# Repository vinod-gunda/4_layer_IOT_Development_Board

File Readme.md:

# 4-Layer ESP32-C3 Development Board

A custom **4-layer ESP32-C3 development board** designed from scratch using **KiCad 10** as part of my embedded systems and PCB design learning.

## Key Features

- ESP32-C3 based controller
- USB-C, USB-UART, Li-Po charging and power management
- SD Card, Flash Memory and sensor interfaces
- 4-layer PCB with power and GND distribution

## PCB Design Skills

- Custom schematic symbol design
- Custom footprint design
- Custom logo-to-footprint conversion
- Hierarchical schematic design
- PCB layout, routing and DRC verification

## Tools & Technology

- **KiCad 10**
- **ESP32-C3**
- **4-Layer PCB**

## Repository Contents

- KiCad schematic files
- PCB layout files
- Custom symbols and footprints
- Project images

## Purpose

This project was developed for **learning, prototyping, and improving practical PCB design skills**.

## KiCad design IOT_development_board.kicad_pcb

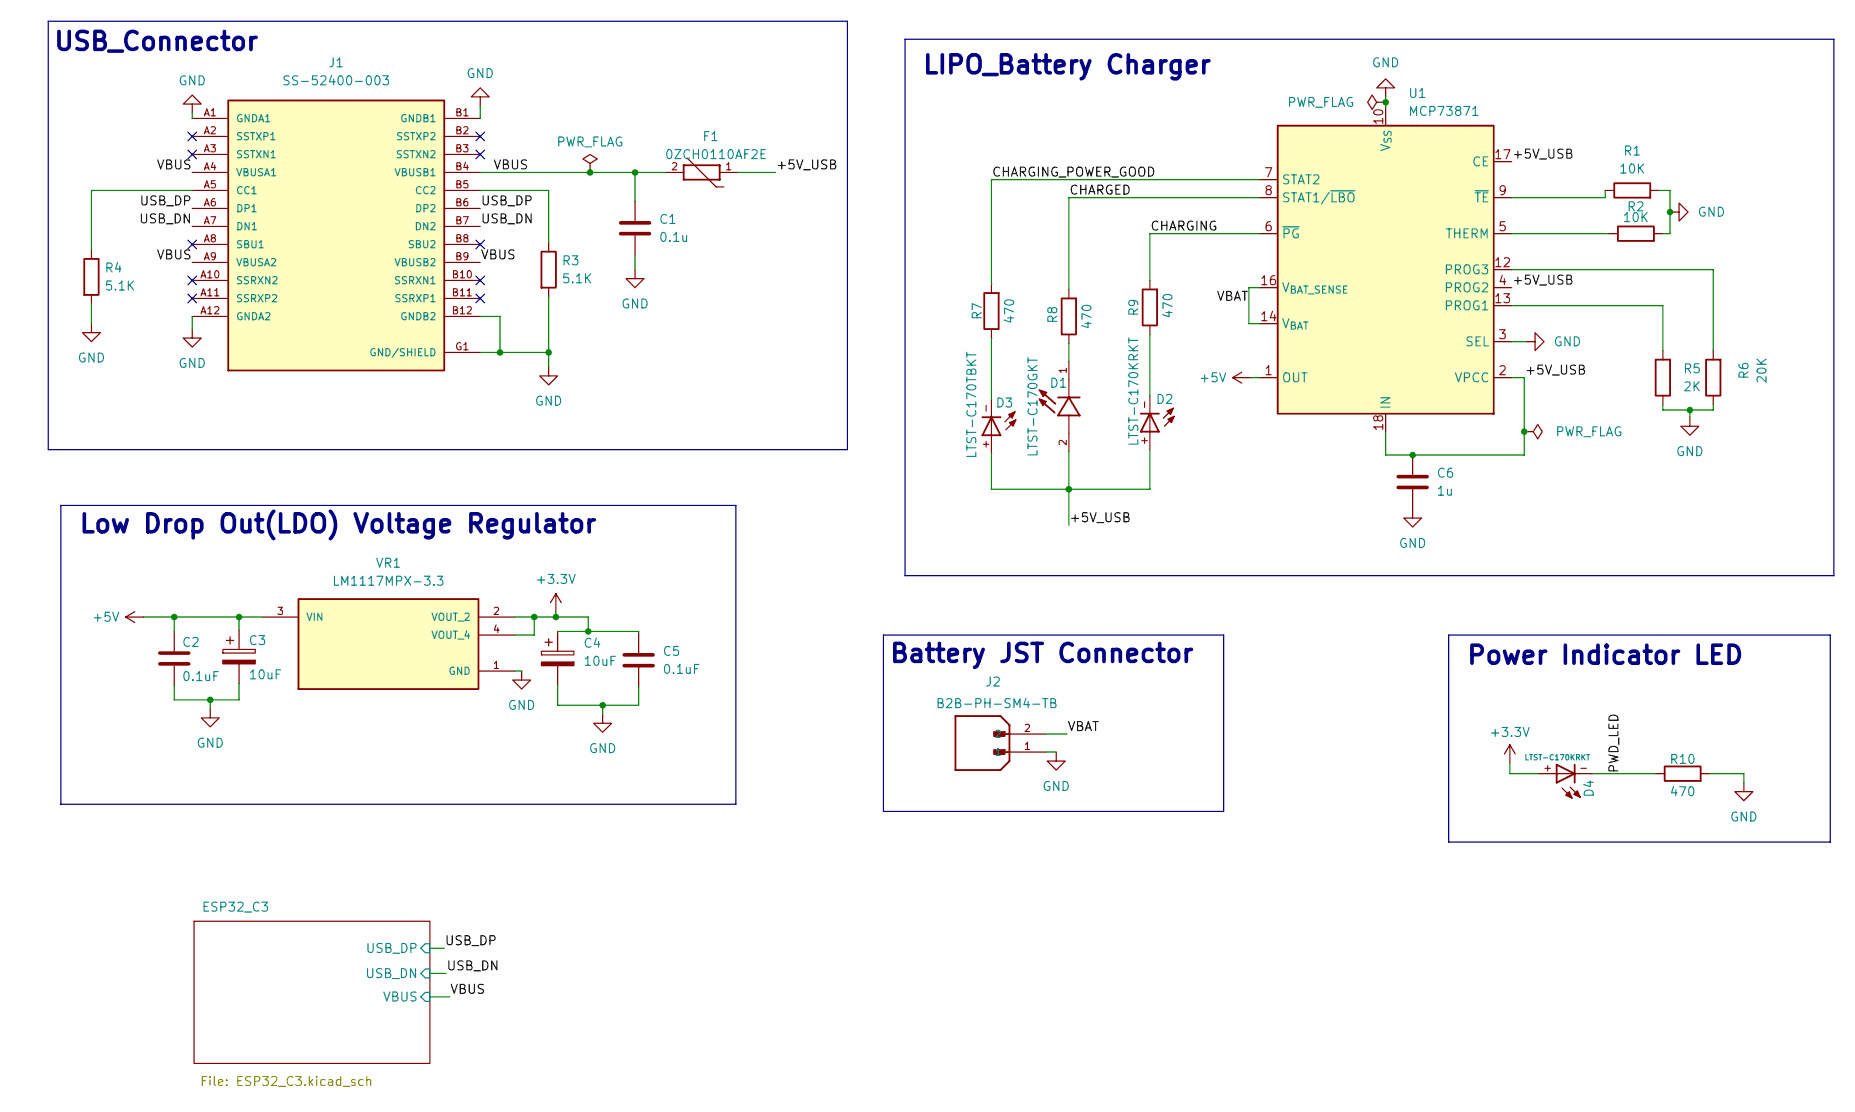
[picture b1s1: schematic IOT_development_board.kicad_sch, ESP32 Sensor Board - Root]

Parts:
C1: 0.1u; C_0805_2012Metric
C2, C5: 0.1uF; C_0805_2012Metric
C3, C4: 10uF; CT1206
C6: 1u; C_0805_2012Metric
D1: LTST-C170GKT; LED_LTST-C170GKT; PARTREV I
D2, D4: LTST-C170KRKT; DIOC200X125X110
D3: LTST-C170TBKT; DIOC200X125X110
F1: 0ZCH0110AF2E; FUSC3225X100N; PARTREV Apr2023
J1: SS-52400-003; BELFUSE_SS-52400-003; PARTREV A0
J2: B2B-PH-SM4-TB; JST_B2B-PH-SM4-TB; PARTREV N/A
R1, R2: 10K; R_0805_2012Metric
R3, R4: 5.1K; R_0805_2012Metric
R5: 2K; R_0805_2012Metric
R6: 20K; R_0805_2012Metric
R7, R8, R9, R10: 470; R_0805_2012Metric
U1: MCP73871; QFN-20-1EP_4x4mm_P0.5mm_EP2.5x2.5mm
VR1: LM1117MPX-3.3; VREG_LM1117MPX-3.3; PARTREV O

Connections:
+3.3V: C4.1, C5.1, D4.+, VR1.2 (VOUT_2), VR1.4 (VOUT_4); also elsewhere on the board
+5V: C2.1, C3.1, U1.1 (OUT), U1.20 (OUT), VR1.3 (VIN)
/+5V_USB: C6.1, D1.2, D2.+, D3.+, F1.1, U1.2 (VPCC), U1.4 (PROG2), U1.17 (CE), U1.18 (IN), U1.19 (IN)
/CHARGED: R8.2, U1.8 (STAT1/~LBO)
/CHARGING: R9.2, U1.6 (~PG)
/CHARGING_POWER_GOOD: R7.2, U1.7 (STAT2)
/PWD_LED: D4.-, R10.1
/USB_DN: J1.A7 (DN1), J1.B7 (DN2); also elsewhere on the board
/USB_DP: J1.A6 (DP1), J1.B6 (DP2); also elsewhere on the board
/VBAT: J2.2, U1.14 (V_{BAT}), U1.15 (V_{BAT}), U1.16 (V_{BAT_SENSE})
/VBUS: C1.1, F1.2, J1.A4 (VBUSA1), J1.A9 (VBUSA2), J1.B4 (VBUSB1), J1.B9 (VBUSB2); also elsewhere on the board
GND: C1.2, C2.2, C3.2, C4.2, C5.2, C6.2, J1.A1 (GNDA1), J1.A12 (GNDA2), J1.B1 (GNDB1), J1.B12 (GNDB2), J1.G1 (GND/SHIELD), J1.G2 (GND/SHIELD), J1.G3 (GND/SHIELD), J1.G4 (GND/SHIELD), J1.S1 (GND/SHIELD), J1.S2 (GND/SHIELD), J1.S3 (GND/SHIELD), J1.S4 (GND/SHIELD), J2.1, R1.2, R2.2, R3.2, R4.2, R5.1, R6.1, R10.2, U1.3 (SEL), U1.10 (V_{SS}), U1.11 (V_{SS}), U1.21 (V_{SS}), VR1.1 (GND); also elsewhere on the board
unnamed: D1.1, R8.1
unnamed: D2.-, R9.1
unnamed: D3.-, R7.1
unnamed: J1.A5 (CC1), R4.1
unnamed: J1.B5 (CC2), R3.1
unnamed: R5.2, U1.13 (PROG1)
unnamed: R6.2, U1.12 (PROG3)
unnamed: R2.1, U1.5 (THERM)
unnamed: R1.1, U1.9 (~TE)

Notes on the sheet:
LIPO_Battery Charger
Battery JST Connector
Power Indicator LED
Low Drop Out(LDO) Voltage Regulator
USB_Connector

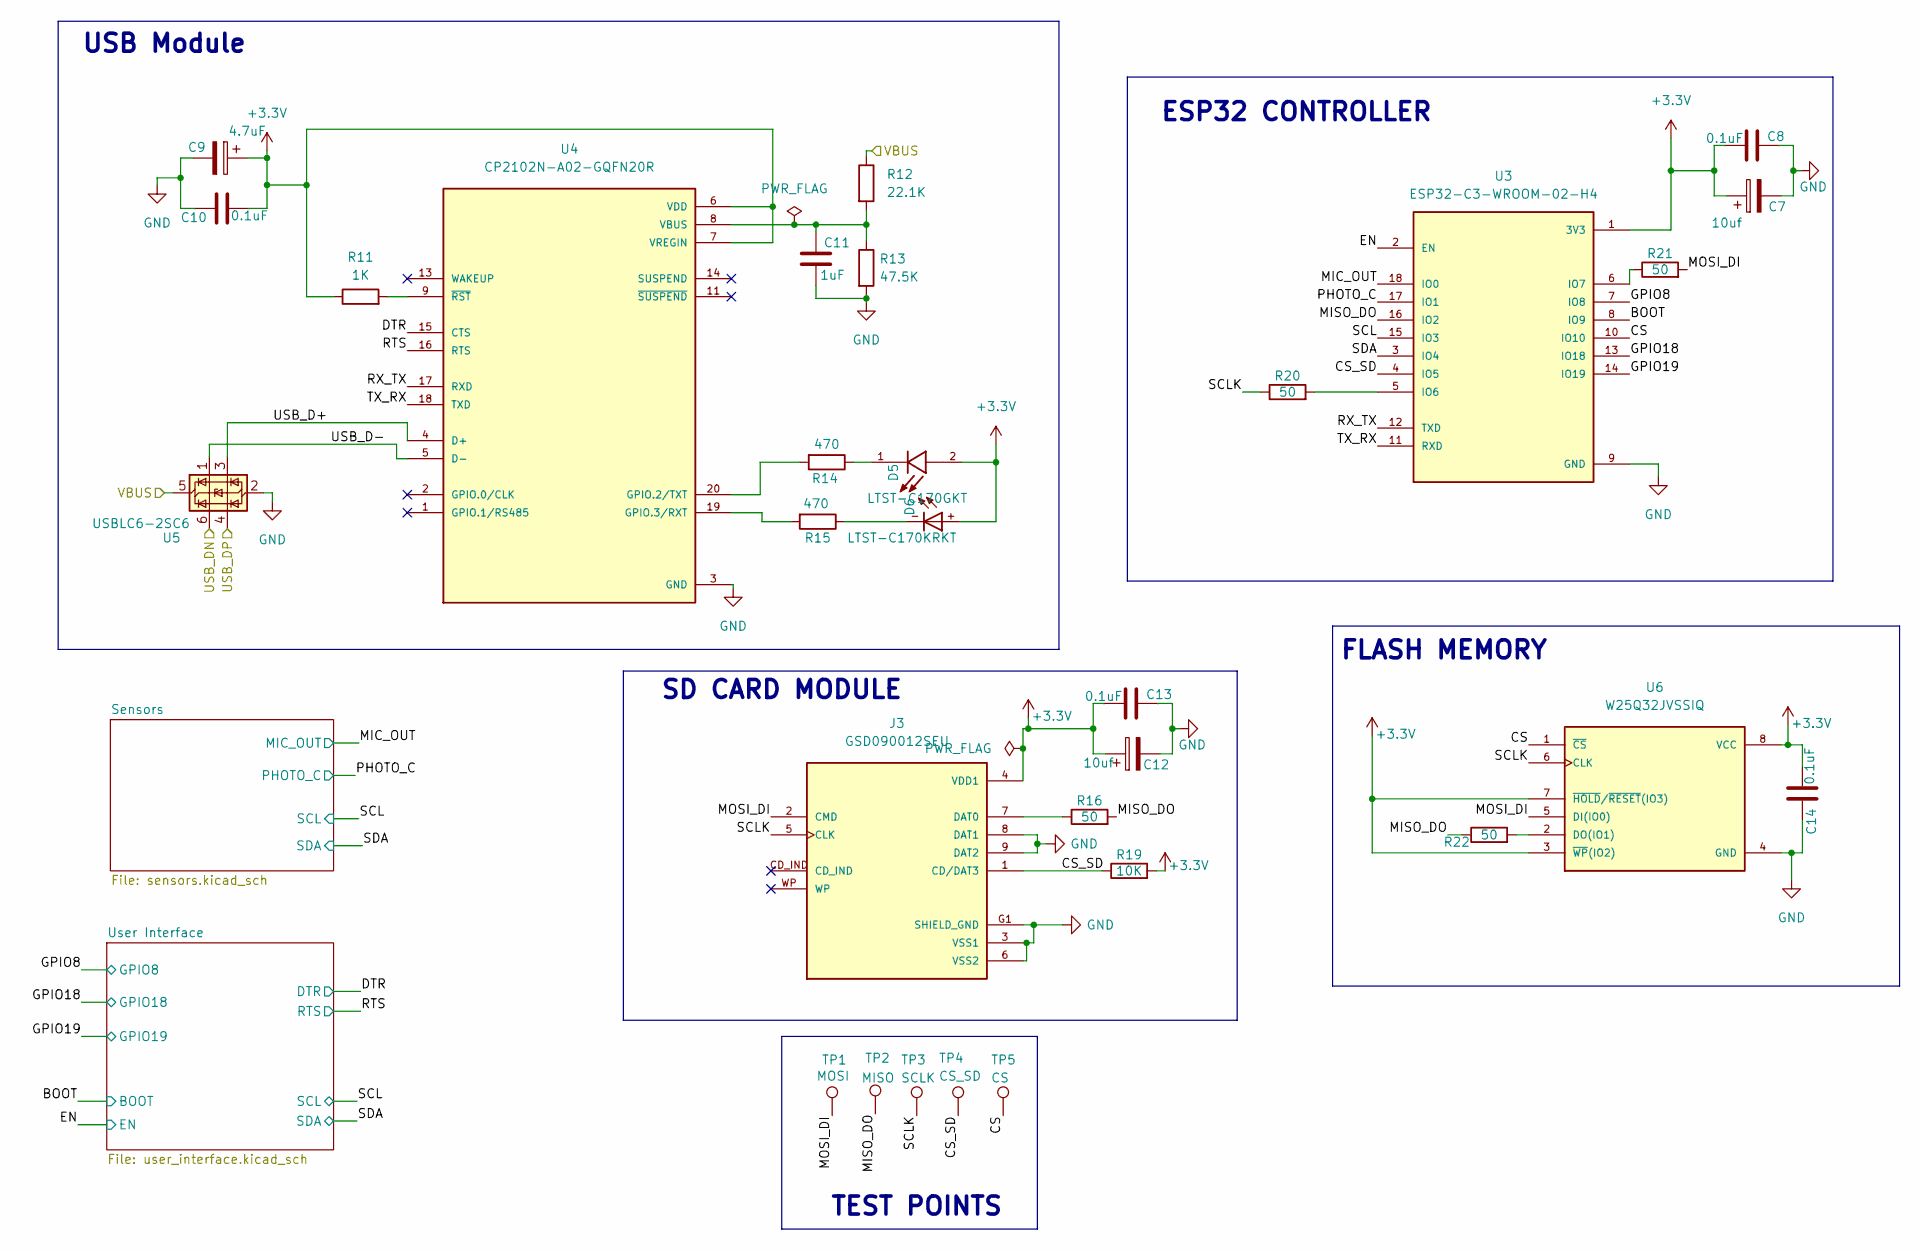
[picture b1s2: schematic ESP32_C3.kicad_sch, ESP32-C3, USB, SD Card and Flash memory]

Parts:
C7, C12: 10uf; CT1206
C8, C10, C13, C14: 0.1uF; C_0805_2012Metric
C9: 4.7uF; CT1206
C11: 1uF; C_0805_2012Metric
D5: LTST-C170GKT; LED_LTST-C170GKT; PARTREV I
D6: LTST-C170KRKT; DIOC200X125X110
J3: GSD090012SEU; AMPHENOL_GSD090012SEU; PARTREV E
R11: 1K; R_0805_2012Metric
R12: 22.1K; R_0805_2012Metric
R13: 47.5K; R_0805_2012Metric
R14, R15: 470; R_0805_2012Metric
R16, R20, R21, R22: 50; R_0805_2012Metric
R19: 10K; R_0805_2012Metric
TP1: MOSI; TestPoint_Pad_D1.0mm
TP2: MISO; TestPoint_Pad_D1.0mm
TP3: SCLK; TestPoint_Pad_D1.0mm
TP4: CS_SD; TestPoint_Pad_D1.0mm
TP5: CS; TestPoint_Pad_D1.0mm
U3: ESP32-C3-WROOM-02-H4; MODULE_ESP32-C3-WROOM-02-H4
U4: CP2102N-A02-GQFN20R; SILABS_CP2102N-A02-GQFN20R; PARTREV 1.3
U5: USBLC6-2SC6; SOT-23-6
U6: W25Q32JVSSIQ; SOIC127P790X216-8N; M_PART_NUMBER W25QXX

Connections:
+3.3V: C7.1, C8.2, C9.1, C10.2, C12.1, C13.2, C14.2, D5.2, D6.+, J3.4 (VDD1), R11.1, R19.2, U3.1 (3V3), U4.6 (VDD), U4.7 (VREGIN), U6.3 (~WP(IO2)), U6.7 (~HOLD/~RESET(IO3)), U6.8 (VCC); also elsewhere on the board
/ESP32_C3/CS: TP5.1 (1_1), U3.10 (IO10), U6.1 (~CS)
/ESP32_C3/EN: U3.2 (EN); also elsewhere on the board
/ESP32_C3/GPIO8: U3.7 (IO8); also elsewhere on the board
/ESP32_C3/GPIO18: U3.13 (IO18); also elsewhere on the board
/ESP32_C3/GPIO19: U3.14 (IO19); also elsewhere on the board
/ESP32_C3/MISO_DO: R16.2, R22.1, TP2.1 (1_1), U3.16 (IO2)
/ESP32_C3/MOSI_DI: J3.2 (CMD), R21.2, TP1.1 (1_1), U6.5 (DI(IO0))
/ESP32_C3/PHOTO_C: U3.17 (IO1); also elsewhere on the board
/ESP32_C3/RTS: U4.16 (RTS); also elsewhere on the board
/ESP32_C3/RX_TX: U3.12 (TXD), U4.17 (RXD)
/ESP32_C3/SCL: U3.15 (IO3); also elsewhere on the board
/ESP32_C3/SCLK: J3.5 (CLK), R20.1, TP3.1 (1_1), U6.6 (CLK)
/ESP32_C3/SDA: U3.3 (IO4); also elsewhere on the board
/ESP32_C3/TX_RX: U3.11 (RXD), U4.18 (TXD)
/ESP32_C3/USB_D+: U4.4 (D+), U5.3 (I/O2)
/ESP32_C3/USB_D-: U4.5 (D-), U5.1 (I/O1)
/USB_DN: U5.6 (I/O1); also elsewhere on the board
/USB_DP: U5.4 (I/O2); also elsewhere on the board
/VBUS: R12.1, U5.5 (VBUS); also elsewhere on the board
GND: C7.2, C8.1, C9.2, C10.1, C11.2, C12.2, C13.1, C14.1, J3.3 (VSS1), J3.6 (VSS2), J3.8 (DAT1), J3.9 (DAT2), J3.G1 (SHIELD_GND), J3.G2 (SHIELD_GND), J3.G3 (SHIELD_GND), J3.G4 (SHIELD_GND), R13.2, U3.9 (GND), U3.19 (GND), U3.20 (GND), U3.21 (GND), U3.22 (GND), U3.23 (GND), U3.24 (GND), U3.25 (GND), U3.26 (GND), U3.27 (GND), U3.28 (GND), U3.29 (GND), U3.30 (GND), U3.31 (GND), U3.32 (GND), U3.33 (GND), U3.34 (GND), U3.35 (GND), U3.36 (GND), U3.37 (GND), U3.38 (GND), U3.39 (GND), U4.3 (GND), U4.12 (GND), U4.21 (GND), U5.2 (GND), U6.4 (GND); also elsewhere on the board
unnamed: D5.1, R14.1
unnamed: D6.-, R15.1
unnamed: J3.7 (DAT0), R16.1
unnamed: R20.2, U3.5 (IO6)
unnamed: R21.1, U3.6 (IO7)
unnamed: R14.2, U4.20 (GPIO.2/TXT)
unnamed: R15.2, U4.19 (GPIO.3/RXT)
unnamed: C11.1, R12.2, R13.1, U4.8 (VBUS)
unnamed: R11.2, U4.9 (~RST)
unnamed: R22.2, U6.2 (DO(IO1))

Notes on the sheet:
TEST POINTS
FLASH MEMORY
ESP32 CONTROLLER
SD CARD MODULE
USB Module

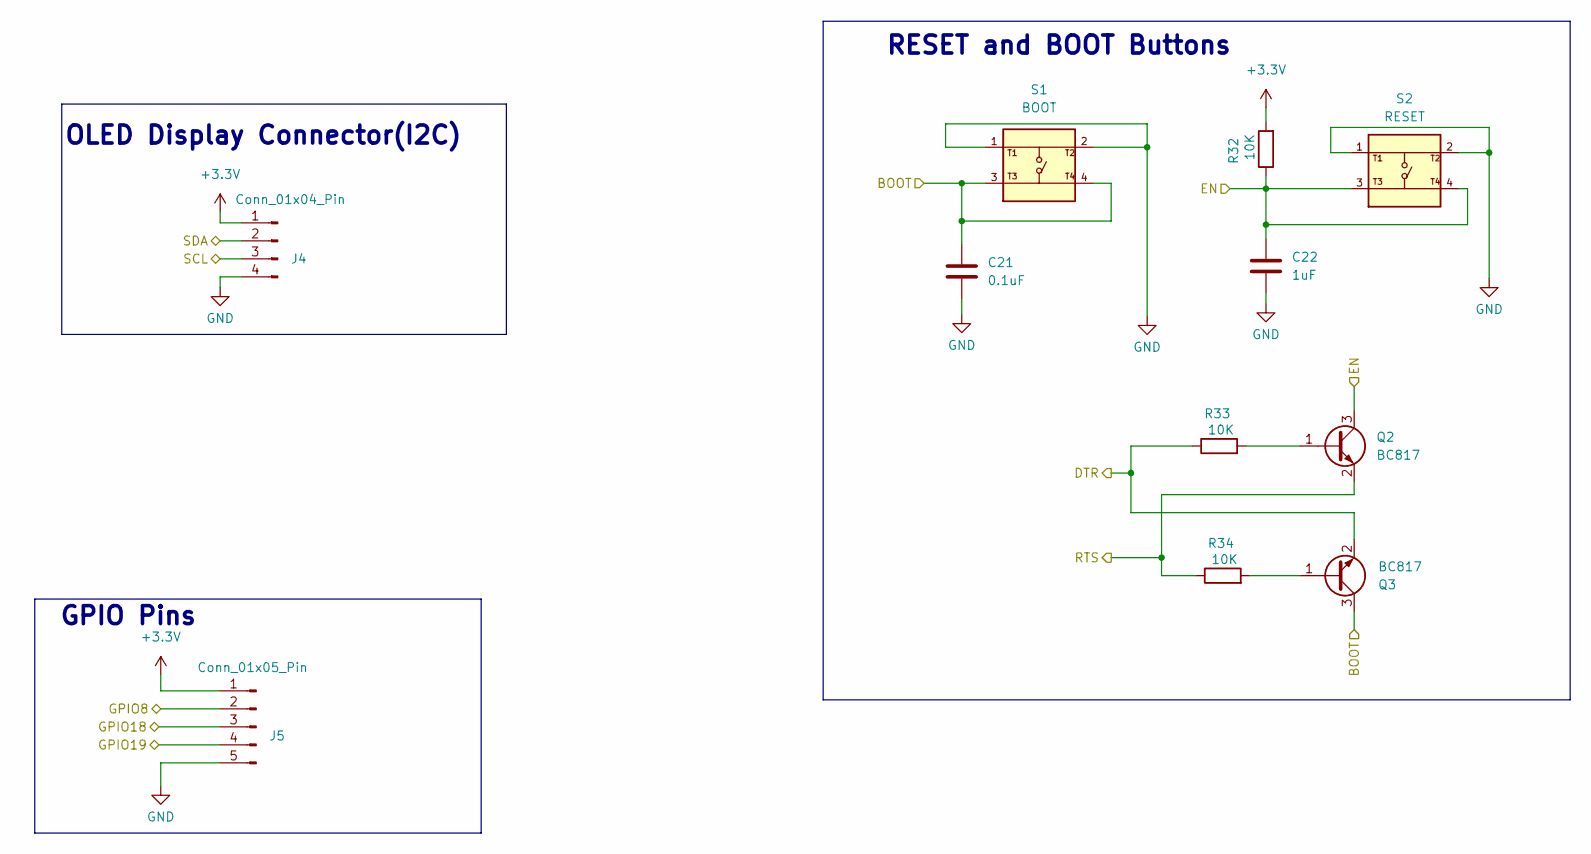
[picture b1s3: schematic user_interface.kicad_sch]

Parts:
C21: 0.1uF; C_0805_2012Metric
C22: 1uF; C_0805_2012Metric
J4: Conn_01x04_Pin; PinHeader_1x04_P2.54mm_Vertical
J5: Conn_01x05_Pin; PinHeader_1x05_P2.54mm_Vertical
Q2, Q3: BC817; SOT-23
R32, R33, R34: 10K; R_0805_2012Metric
S1: BOOT; SW_USLPT2819DT2TR; PARTREV P
S2: RESET; SW_USLPT2819DT2TR; PARTREV P

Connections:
+3.3V: J4.1, J5.1, R32.2; also elsewhere on the board
/ESP32_C3/EN: C22.1, Q2.3 (C), R32.1, S2.3, S2.4; also elsewhere on the board
/ESP32_C3/GPIO8: J5.2; also elsewhere on the board
/ESP32_C3/GPIO18: J5.3; also elsewhere on the board
/ESP32_C3/GPIO19: J5.4; also elsewhere on the board
/ESP32_C3/RTS: Q2.2 (E), R34.1; also elsewhere on the board
/ESP32_C3/SCL: J4.3; also elsewhere on the board
/ESP32_C3/SDA: J4.2; also elsewhere on the board
GND: C21.2, C22.2, J4.4, J5.5, S1.1, S1.2, S2.1, S2.2; also elsewhere on the board
unnamed: Q2.1 (B), R33.2
unnamed: Q3.1 (B), R34.2

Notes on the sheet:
OLED Display Connector(I2C)
RESET and BOOT Buttons
GPIO Pins

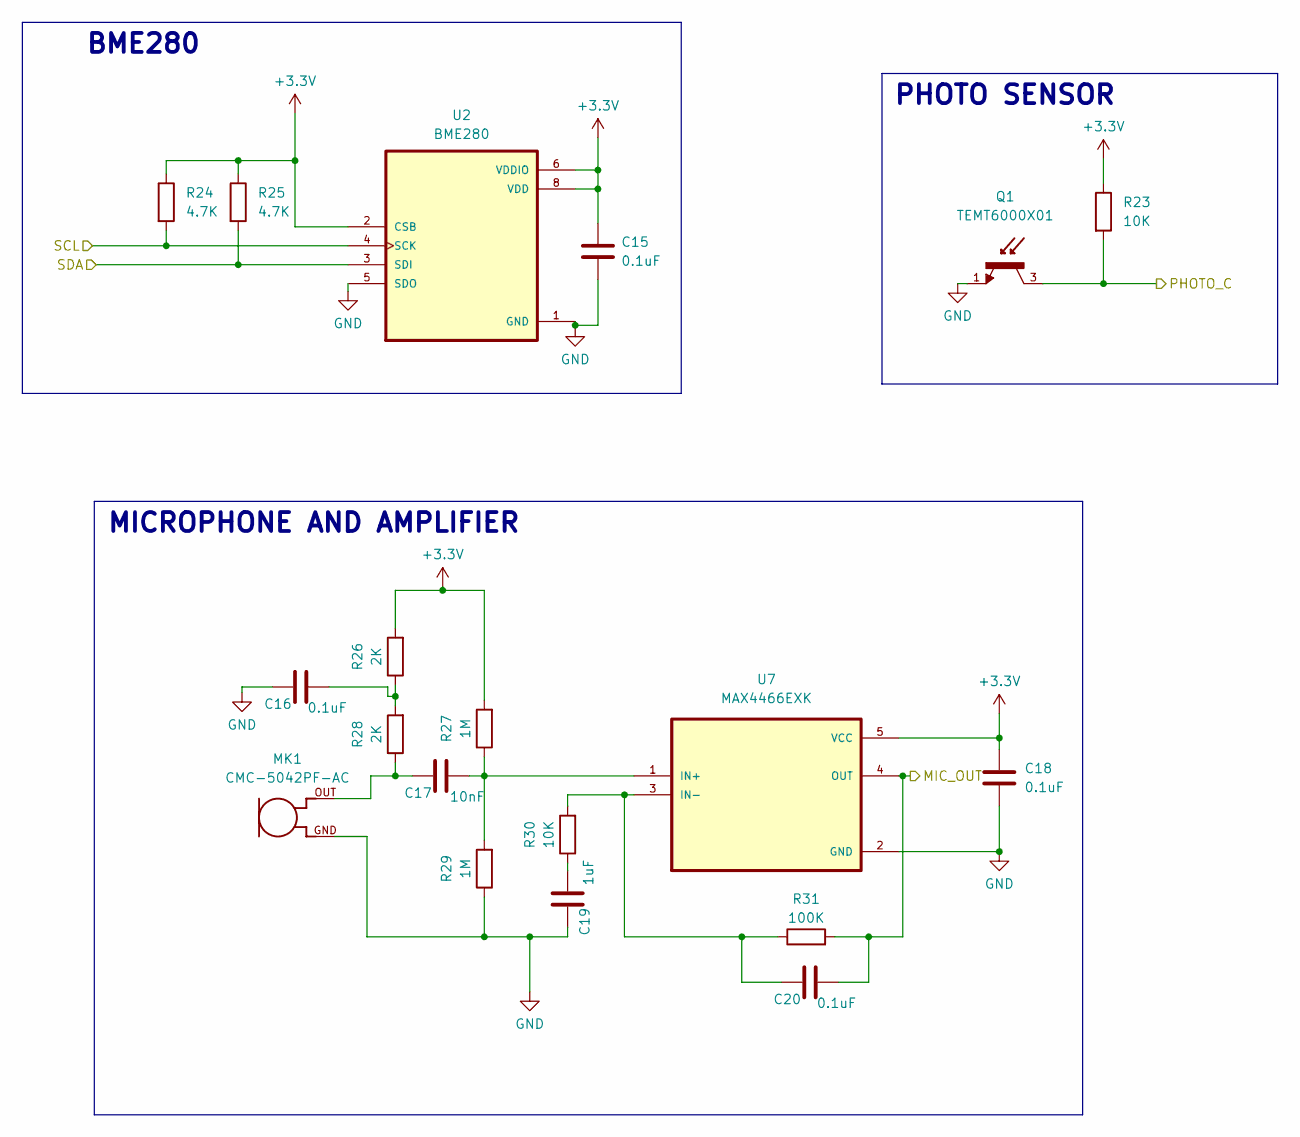
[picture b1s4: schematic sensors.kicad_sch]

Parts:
C15, C16, C18, C20: 0.1uF; C_0805_2012Metric
C17: 10nF; C_0805_2012Metric
C19: 1uF; C_0805_2012Metric
MK1: CMC-5042PF-AC; CUI_CMC-5042PF-AC
Q1: TEMT6000X01; TRANS_TEMT6000X01; PARTREV 1.9
R23, R30: 10K; R_0805_2012Metric
R24, R25: 4.7K; R_0805_2012Metric
R26, R28: 2K; R_0805_2012Metric
R27, R29: 1M; R_0805_2012Metric
R31: 100K; R_0805_2012Metric
U2: BME280; PSON65P250X250X100-8N
U7: MAX4466EXK; SOT65P210X110-5N

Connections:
+3.3V: C15.1, C18.1, R23.1, R24.1, R25.1, R26.2, R27.2, U2.2 (CSB), U2.6 (VDDIO), U2.8 (VDD), U7.5 (VCC); also elsewhere on the board
/ESP32_C3/PHOTO_C: Q1.3, R23.2; also elsewhere on the board
/ESP32_C3/SCL: R24.2, U2.4 (SCK); also elsewhere on the board
/ESP32_C3/SDA: R25.2, U2.3 (SDI); also elsewhere on the board
GND: C15.2, C16.1, C18.2, C19.1, MK1.GND, Q1.1, R29.1, U2.1 (GND), U2.5 (SDO), U2.7 (GND), U7.2 (GND); also elsewhere on the board
unnamed: C16.2, R26.1, R28.2
unnamed: C17.1, MK1.OUT, R28.1
unnamed: C19.2, R30.1
unnamed: C17.2, R27.1, R29.2, U7.1 (IN+)
unnamed: C20.1, R30.2, R31.1, U7.3 (IN-)

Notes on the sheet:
BME280
MICROPHONE AND AMPLIFIER
PHOTO SENSOR

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
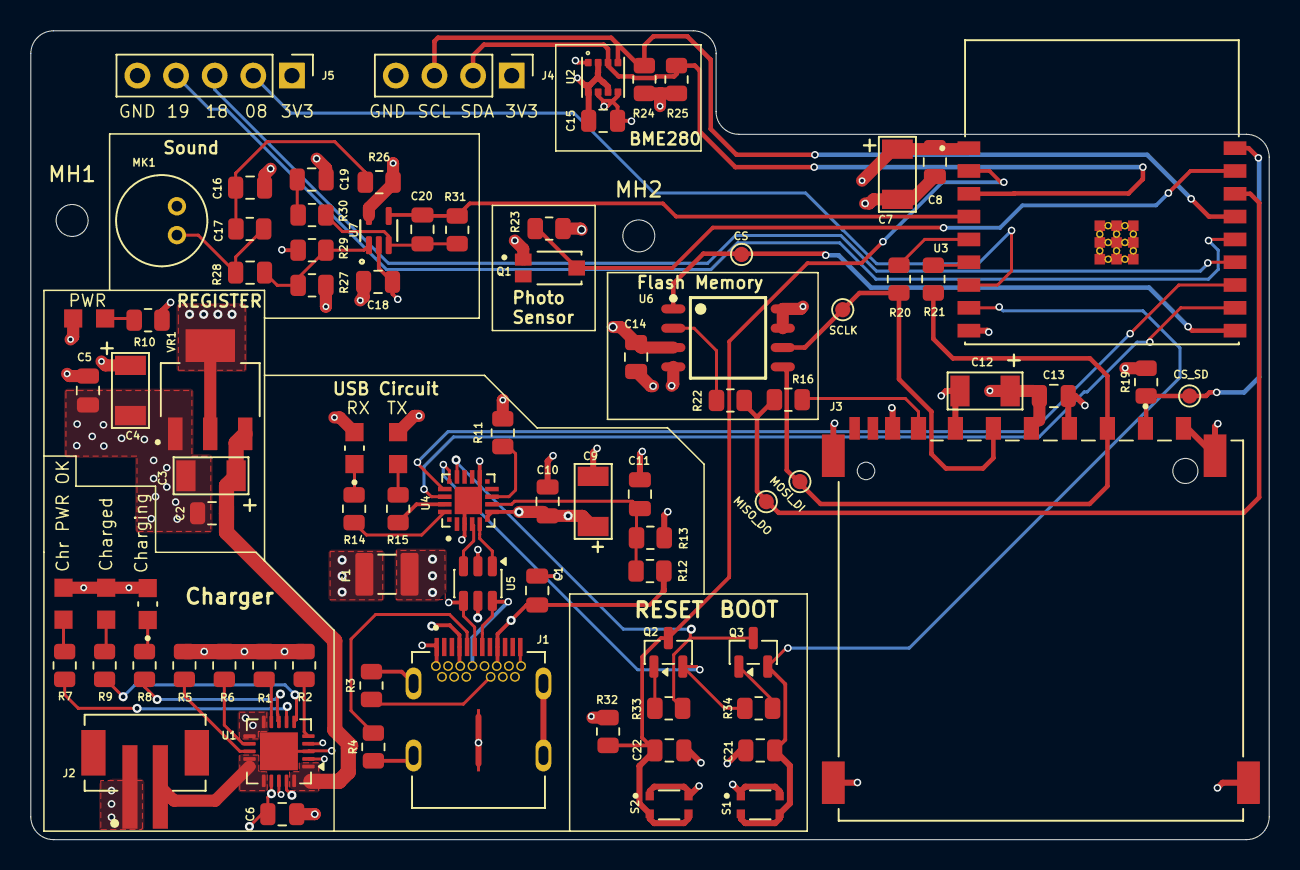
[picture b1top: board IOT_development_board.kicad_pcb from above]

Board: 4 copper layers, 81.4 x 53.2 mm, 87 parts (0 on the bottom side), 58 nets.

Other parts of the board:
MH1, MH2: MountingHole_2.1mm
